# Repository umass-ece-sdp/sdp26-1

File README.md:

# SDP26 Team 1 | FALCON – Filming Autonomous Learning and Cinematic Optic Navigator

Autonomous DJI Tello target-tracking platform with a wearable glove controller. A Jetson host (or Linux laptop) runs vision and flight control while an ESP32-S3 glove sends discrete range commands over Wi-Fi. The system locks onto a target, keeps the subject centered and at a commanded distance, searches when lost, and lands safely on failure.

---

## Repository Map

- [software/src/main.py](software/src/main.py): Entry point - connects to Tello drone and ESP32 glove AP, starts the glove client and drone tracking threads
- [software/lib/falcon_vision.py](software/lib/falcon_vision.py): Vision + control loop, distance mapping from glove instructions, safety land/search logic
- [software/lib/falcon.py](software/lib/falcon.py): DJI Tello wrapper that auto-connects to the drone Wi-Fi using a provided interface/SSID
- [hardware/firmware](hardware/firmware): ESP32-S3 glove firmware with WiFi AP and TCP server, plus Python client for base station
- [software/scripts](software/scripts): Network helper scripts (WiFi AP setup for Tello and glove connections) and startup helper for the host
- [docs](docs): Design docs placeholders (currently empty); fill as deliverables are produced

---

## System Overview

- **Vision/Control (host):** Tracks a target in the Tello video feed, computes yaw/altitude/forward corrections, and commands the drone. Falls back to search spins when target is lost; lands after timeout or manual quit (press `q`). See [software/lib/falcon_vision.py](software/lib/falcon_vision.py).
- **Glove (ESP32-S3 DevKitC-1):** Four three-state switches encode a 4-char string (LR, FB, heading, altitude). Reads IMU and stretch sensors, computes hand velocity, packages data into 6-float packets, and sends to base station. Also creates the WiFi AP. See [hardware/firmware/main/glove.cpp](hardware/firmware/main/glove.cpp) and [hardware/firmware/main/wifi_server.cpp](hardware/firmware/main/wifi_server.cpp).
- **Networking:** The **ESP32 glove creates a WiFi AP** named **"FALCON-Glove"** (password: `team1-falcon`) on 192.168.4.0/24 and runs a **TCP server at 192.168.4.1:5000**. The **base station (host) connects as a client** to this AP and connects to the glove's TCP server. Separately, the base station connects to the Tello drone on its own WiFi SSID using a second interface. See [hardware/firmware/main/wifi_server.h](hardware/firmware/main/wifi_server.h) and [hardware/firmware/glove_client.py](hardware/firmware/glove_client.py) for configuration.

---

## Hardware

- DJI Tello drone.
- ESP32-S3-DevKitC-1 (Arduino/PlatformIO) running glove sensors and WiFi AP + TCP server.
- Four 3-state switches wired to pins (LR: GPIO4/5, FB: 6/7, Heading: 15/16, Altitude: 17/18). See [hardware/firmware/main/glove.cpp](hardware/firmware/main/glove.cpp).
- Host computer (Jetson Nano, Linux laptop, or Windows machine) with **two WiFi interfaces**: one for Tello drone, one for glove AP.

---

## Firmware (Glove) Setup

1. Install PlatformIO.
2. From [hardware/firmware](hardware/firmware):
   - Build: `platformio run -e client`
   - Flash: `platformio run -e client -t upload`
   - Serial monitor: `platformio device monitor -e client`
3. WiFi/Server config lives in [hardware/firmware/main/wifi_server.h](hardware/firmware/main/wifi_server.h):
   - **AP_SSID:** `FALCON-Glove` (the AP name the glove creates)
   - **AP_PASS:** `team1-falcon` (glove AP password)
   - **AP IP:** `192.168.4.1/24` (glove runs TCP server here)
   - **PORT:** `5000` (TCP server port on glove)
4. Glove reads sensors, creates a 6-float packet (fingers[4], speed, distance) every ~90ms, and sends it to any connected base station client. See [hardware/firmware/main/wifi_server.cpp](hardware/firmware/main/wifi_server.cpp).

---

## Software Prereqs

- Python 3.10+
- Dependencies: djitellopy, opencv-python, numpy, ultralytics (declared in [pyproject.toml](pyproject.toml)).

Install (recommended in a virtualenv):

```bash
pip install -e .
```

---

## Network Setup (Host / Base Station)

**Architecture:** Glove (ESP32) is the TCP server; base station (host) is the client.

### Prerequisites

- **Glove powered on first** — It creates AP "FALCON-Glove" and starts TCP server at 192.168.4.1:5000
- **Base station has two WiFi interfaces:**
  - **Interface 1:** Connects to Tello drone SSID (e.g., "TELLO-FE046A")
  - **Interface 2:** Connects to glove AP "FALCON-Glove"

### Automatic Setup (Linux with 2 interfaces)

```bash
sudo bash software/scripts/setup_wifi.sh TELLO-FE046A "" FALCON-Glove team1-falcon
```

This script:
1. Connects Interface 1 to Tello SSID
2. Connects Interface 2 to glove AP "FALCON-Glove"
3. Verifies connectivity to both networks

### Manual Setup (Windows or Single Interface)

**For Tello:**
1. Go to **Settings → Network & Internet → WiFi**
2. Connect to **TELLO-FE046A** (empty password)

**For Glove:**
1. Go to **Settings → Network & Internet → WiFi**
2. Connect to **FALCON-Glove** (password: `team1-falcon`)
3. You should get assigned an IP like 192.168.4.x

**Verify both connections:**
```bash
ping 192.168.1x.x.x.x     # Tello IP
ping 192.168.4.1          # Glove server
```

---

## Running the System

### Startup Sequence

1. **Power on the ESP32 glove first:**
   - Creates WiFi AP "FALCON-Glove"
   - Starts TCP server at 192.168.4.1:5000
   - Waits for base station client connection

2. **On the base station, ensure both WiFi connections are active:**
   - Connected to Tello SSID
   - Connected to "FALCON-Glove" AP

3. **Run the main program:**

   ```bash
   python -m software.src.main
   ```

   This will:
   - Connect to the Tello drone and request SDK mode
   - Connect to the glove's TCP server at 192.168.4.1:5000
   - Wait for glove connection (serial monitor should show "[SERVER] Base station connected from...")
   - Take off and begin tracking the target
   - Respond to glove sensor input and gesture commands

### Expected Output

**Glove Serial Monitor:**
```
[AP] Access Point created successfully!
[AP] SSID: FALCON-Glove
[AP] IP Address: 192.168.4.1
[SERVER] Base station connected from: 192.168.4.x
[SERVER] Sent packet (24 bytes)
```

**Base Station Terminal:**
```
[CLIENT] Connecting to glove server at 192.168.4.1:5000...
[CLIENT] Connected to glove server!
Binding complete
Connected with 192.168.4.1: 5000
```

---

## Glove Instruction Mapping (distance presets)

- `0000` → target distance 50 cm
- `1000` → target distance 25 cm
- `2000` → target distance 100 cm

Other patterns are logged but ignored for distance changes. The vision loop re-computes target area each time a mapped pattern arrives.

---

## Behavior and Safety

- Hover/search: If the target disappears, the drone yaws to search; after a timeout it lands.
- Manual exit: Press `q` in the vision window to land and stop.
- Connection failures: Tello Wi-Fi connect failures abort startup; glove disconnects clear the shared state in [software/lib/variables.py](software/lib/variables.py).
- Stream cleanup: On any exit path, video stream is stopped and RC commands zeroed before ending.

---

## Development Notes

- Vision currently uses HSV color masking; YOLO detection code is present but commented out. Tweak target color, tolerances, and speeds near the top of [software/lib/falcon_vision.py](software/lib/falcon_vision.py).
- Empty doc folders contain `.gitkeep`; populate [docs/design_specs](docs/design_specs) and [docs/final_report](docs/final_report) as artifacts are produced.
- No automated tests yet; add unit tests under `software/tests/` and leverage PlatformIO monitors for firmware.

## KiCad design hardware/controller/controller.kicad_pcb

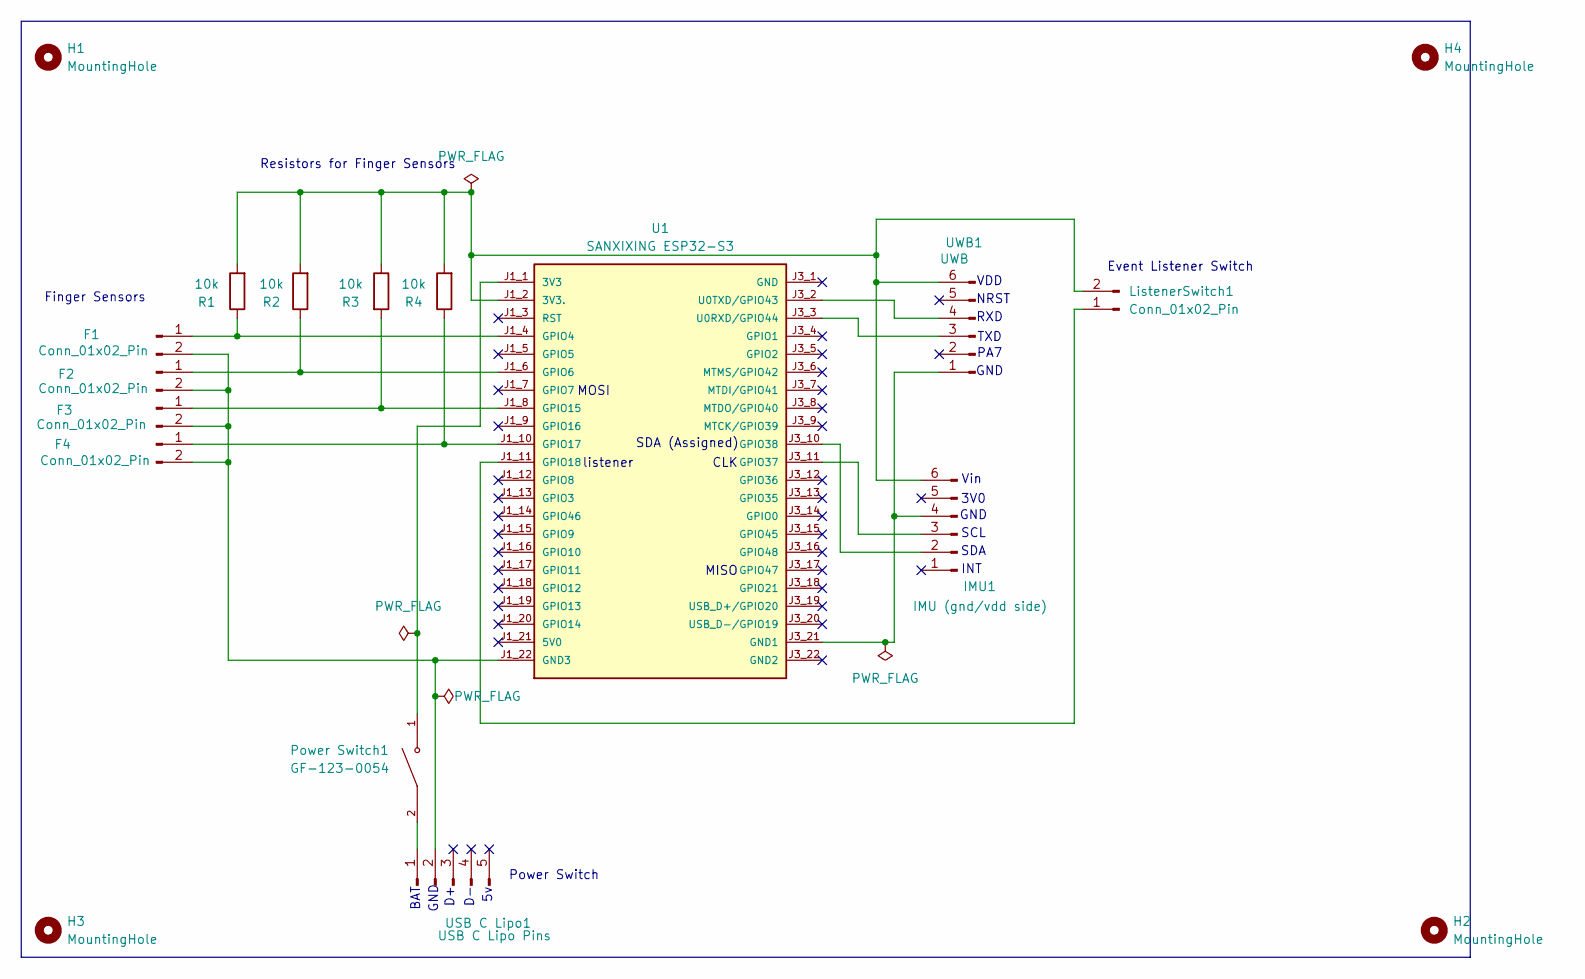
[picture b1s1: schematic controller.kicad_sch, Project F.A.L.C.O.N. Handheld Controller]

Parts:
F1, F2, F3, F4: Conn_01x02_Pin; PinSocket_1x02_P2.54mm_Vertical
H1, H2, H3, H4: MountingHole; MountingHole_3.2mm_M3
IMU1: IMU (gnd/vdd side); PinSocket_1x06_P2.54mm_Vertical
ListenerSwitch1: Conn_01x02_Pin; PinSocket_1x02_P2.54mm_Vertical
Power Switch1: GF-123-0054; SW_GF-123-0054; PARTREV May 20, 2003
R1, R2, R3, R4: 10k; R_Axial_DIN0204_L3.6mm_D1.6mm_P5.08mm_Horizontal
U1: SANXIXING ESP32-S3; SANXIXING-ESP32-S3
USB C Lipo1: USB C Lipo Pins; PinSocket_1x05_P2.54mm_Vertical
UWB1: UWB; PinSocket_1x06_P2.54mm_Vertical

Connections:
unnamed 0: F1.1, R1.1, U1.J1_4 (GPIO4); also elsewhere on the board
unnamed 1: F1.2, F2.2, F3.2, F4.2, U1.J1_22 (GND3), USB C Lipo1.2; also elsewhere on the board
unnamed 2: F2.1, R2.1, U1.J1_6 (GPIO6); also elsewhere on the board
unnamed 3: F3.1, R3.2, U1.J1_8 (GPIO15); also elsewhere on the board
unnamed 4: F4.1, R4.1, U1.J1_10 (GPIO17); also elsewhere on the board
unnamed 5: IMU1.2, U1.J3_10 (GPIO38); also elsewhere on the board
unnamed 6: IMU1.3, U1.J3_11 (GPIO37); also elsewhere on the board
unnamed 7: IMU1.4, U1.J3_21 (GND1), UWB1.1; also elsewhere on the board
unnamed 8: IMU1.6, ListenerSwitch1.2, R1.2, R2.2, R3.1, R4.2, U1.J1_2 (3V3.), UWB1.6; also elsewhere on the board
unnamed 9: ListenerSwitch1.1, U1.J1_11 (GPIO18); also elsewhere on the board
unnamed 10: Power Switch1.1, U1.J1_1 (3V3); also elsewhere on the board
unnamed 11: U1.J3_3 (U0RXD/GPIO44), UWB1.3; also elsewhere on the board
unnamed 12: U1.J3_2 (U0TXD/GPIO43), UWB1.4; also elsewhere on the board
unnamed: Power Switch1.2, USB C Lipo1.1

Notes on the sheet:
INT
TXD
Power Switch
VDD
NRST
GND
Vin
PA7
SDA
MISO
SCL
3V0
BAT
Resistors for Finger Sensors
Event Listener Switch
SDA (Assigned)
MOSI
RXD
CLK
listener
Finger Sensors

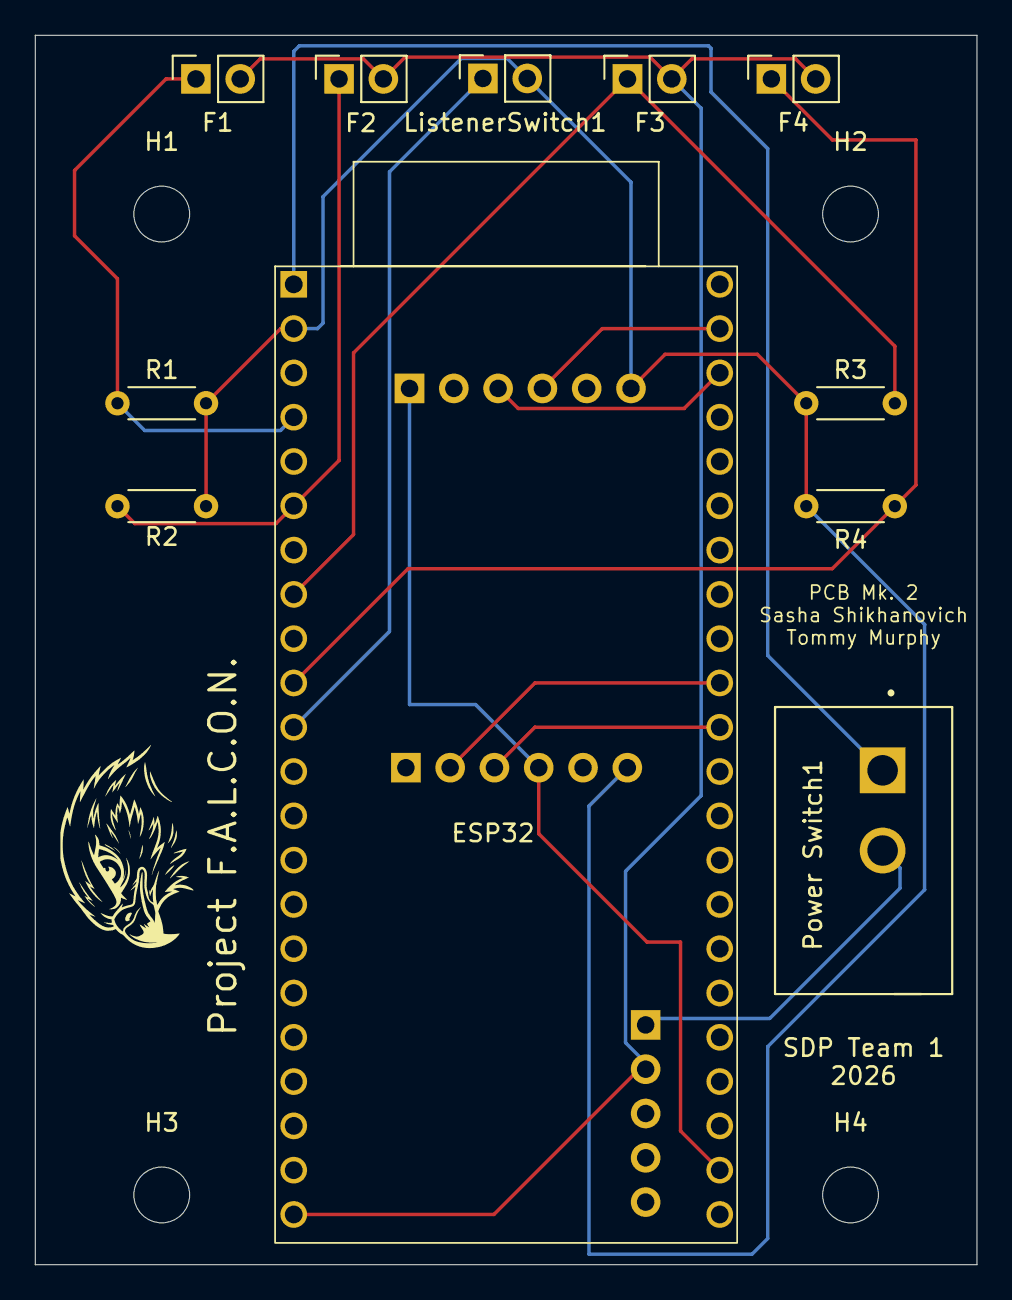
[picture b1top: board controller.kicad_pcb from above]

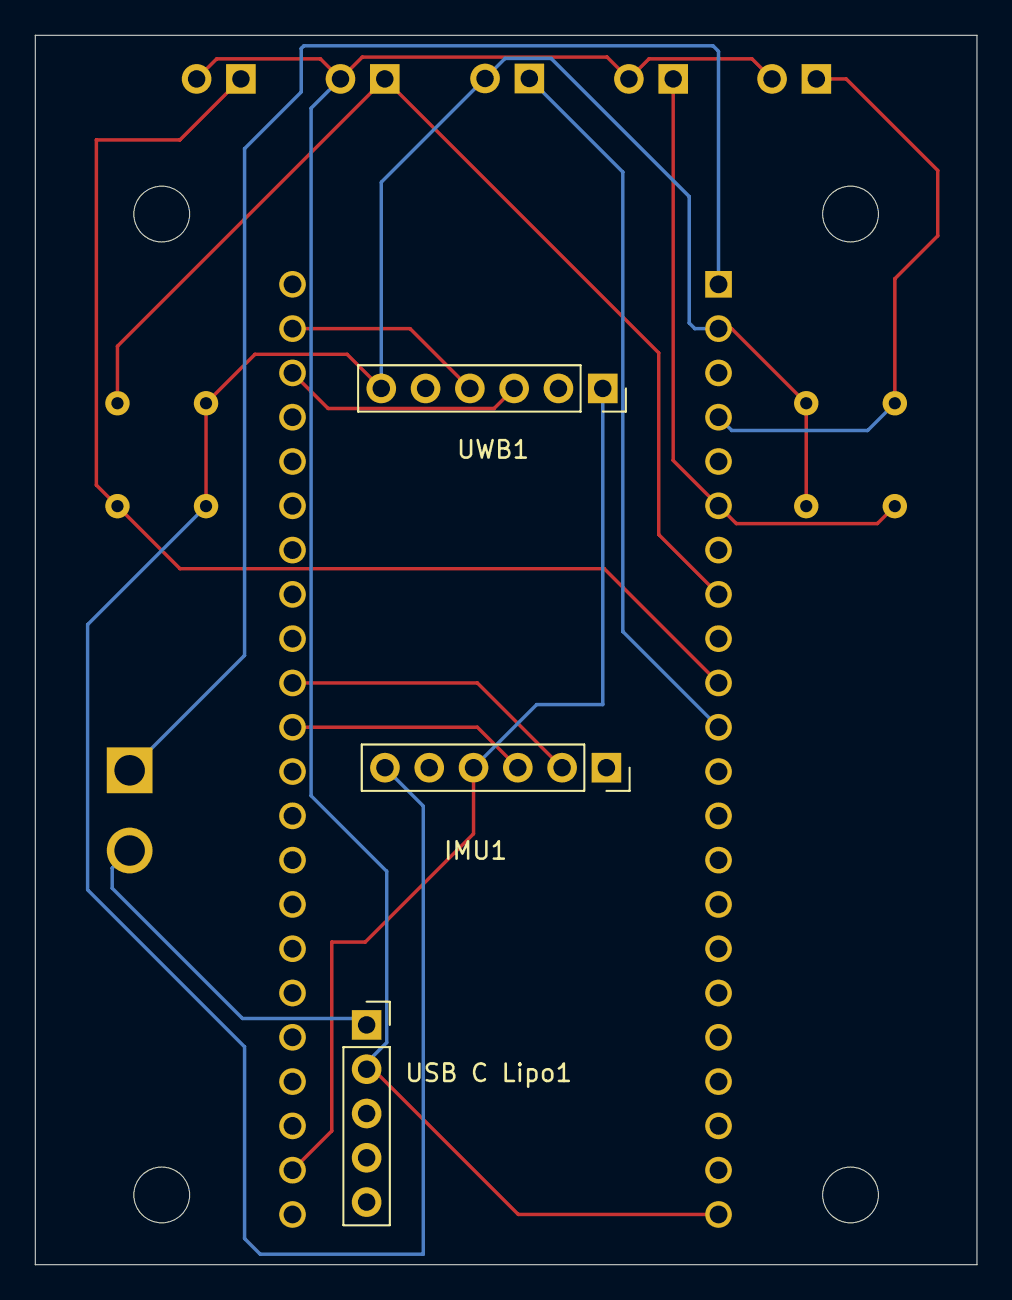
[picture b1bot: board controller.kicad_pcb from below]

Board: 2 copper layers, 54.0 x 70.5 mm, 19 parts (3 on the bottom side), 14 nets.

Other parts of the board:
ESP32: SANXIXING ESP32-S3; SANXIXING-ESP32-S3
Project F.A.L.C.O.N.: LOGO

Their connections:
unnamed 0: ESP32.J1_4 (GPIO4); also elsewhere on the board
unnamed 1: ESP32.J1_22 (GND3); also elsewhere on the board
unnamed 2: ESP32.J1_6 (GPIO6); also elsewhere on the board
unnamed 3: ESP32.J1_8 (GPIO15); also elsewhere on the board
unnamed 4: ESP32.J1_10 (GPIO17); also elsewhere on the board
unnamed 5: ESP32.J3_10 (GPIO38); also elsewhere on the board
unnamed 6: ESP32.J3_11 (GPIO37); also elsewhere on the board
unnamed 7: ESP32.J3_21 (GND1); also elsewhere on the board
unnamed 8: ESP32.J1_2 (3V3.); also elsewhere on the board
unnamed 9: ESP32.J1_11 (GPIO18); also elsewhere on the board
unnamed 10: ESP32.J1_1 (3V3); also elsewhere on the board
unnamed 11: ESP32.J3_3 (U0RXD/GPIO44); also elsewhere on the board
unnamed 12: ESP32.J3_2 (U0TXD/GPIO43); also elsewhere on the board

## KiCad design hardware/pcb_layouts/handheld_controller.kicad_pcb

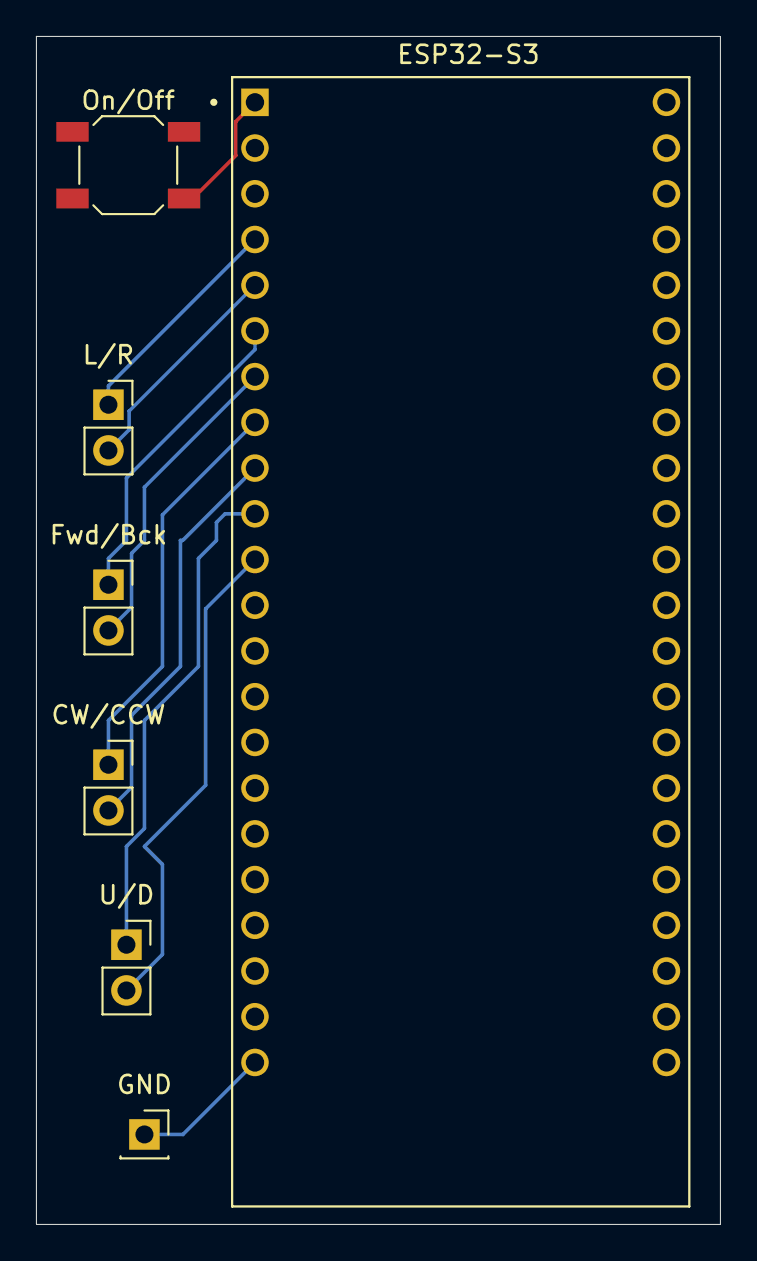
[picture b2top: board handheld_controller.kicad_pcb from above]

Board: 2 copper layers, 38.0 x 66.0 mm, 7 parts (0 on the bottom side), 10 nets.

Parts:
CW/CCW: Conn_01x02_Pin; PinSocket_1x02_P2.54mm_Vertical
ESP32-S3: ESP32-S3-DEVKITC-1-N8R8
Fwd/Bck: Conn_01x02_Pin; PinSocket_1x02_P2.54mm_Vertical
GND: Conn_01x01_Pin; PinSocket_1x01_P2.54mm_Vertical
L/R : Conn_01x02_Pin; PinSocket_1x02_P2.54mm_Vertical
On/Off: SW_DIP_x01; SW_SPST_SKQG_WithStem
U/D: Conn_01x02_Pin; PinSocket_1x02_P2.54mm_Vertical

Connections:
GND: ESP32-S3.J1_22 (GND3), GND.1
unnamed: ESP32-S3.J1_4 (GPIO4), L/R.1
unnamed: ESP32-S3.J1_5 (GPIO5), L/R.2
unnamed: ESP32-S3.J1_6 (GPIO6), Fwd/Bck.1
unnamed: ESP32-S3.J1_7 (GPIO7), Fwd/Bck.2
unnamed: CW/CCW.1, ESP32-S3.J1_8 (GPIO15)
unnamed: CW/CCW.2, ESP32-S3.J1_9 (GPIO16)
unnamed: ESP32-S3.J1_10 (GPIO17), U/D.1
unnamed: ESP32-S3.J1_11 (GPIO18), U/D.2
unnamed: ESP32-S3.J1_1 (3V3), On/Off.2

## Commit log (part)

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2025-10-06 Starting code for ACD functions
2025-10-21 initial hardware commit, basic hardware block schem
2025-10-21 Create task of connecting wifi in python
2025-10-21 Change project name
2025-10-21 Inital code for Docker Container
2025-10-22 Added started code for ESP32 WiFi client
2025-10-22 Added bash script for adding connecting to drone's wifi
2025-10-22 Added file searching to get .sh
2025-10-23 Set Falcon to always connect with on-board port
2025-10-23 3d model file
2025-10-23 Some changes to run docker in linux
2025-10-23 Change WiFi to recognize path from root
2025-10-24 Add exit on connection error
2025-10-24 init commit of cv shi
2025-10-24 simplified and documented code
2025-10-24 moved a couple params
2025-11-02 Created pio project for compiling and flashing client code
2025-11-02 Remove old client code (i forgor)
2025-11-02 Switch client to sending strings
2025-11-02 Create/run server to receive instructions from glove
2025-11-03 Move FALCON to lib directory
2025-11-03 Create variables file for shared environment
2025-11-03 Integrate variables into server code
2025-11-03 Start a main file for linking systems
2025-11-04 adding hardware controller serial code
2025-11-04 Link together systems, split into processes
2025-11-04 downloaded yolo locally and searched for it locally
2025-11-04 changed file pathing
2025-11-04 Move/rename glove code
2025-11-04 maybe fixed color tracking issue
2025-11-04 final (ish) schematic with real footprints
2025-11-04 initial pcb file commit
2025-11-04 Changed frame presentation to viewer
2025-11-04 Moved vision code to lib
2025-11-06 acceptably final PCB (passes DRC)
2025-11-06 acceptably final schematic (passes ERC)
2025-11-07 debugging print statements
2025-11-07 update gitignore
2025-11-07 adding main and changing .ini to mac paths
2025-11-07 Created header files for firmware
2025-11-07 Changes to run main in ini
2025-11-07 convert espidf code to arduino
2025-11-07 trying to convert glove code to esp framework (idk if it works)
2025-11-07 using one gitignore
2025-11-07 working connection using arduino
2025-11-11 Add dynamic COM port finding for windows, removed espidf files
2025-11-11 Changing default wifi interface
2025-11-11 print instructions from esp
2025-11-11 adding toml to package falcon
2025-11-11 Added loop for drone process
2025-11-11 Adding sleep
2025-11-11 Revert "Merge branch 'integration-testing' into converting-to-arduino"
    This reverts commit dbe07ec8ee8ab3334bb31f3c9234bafc4f2a2372, reversing
    changes made to 41b58e3be06abe35e6818b64846f8ce6c7973896.
2025-11-11 adding led library
2025-11-12 updating color codes for signal transmission debugging
2025-11-12 stable color set to blue
2025-11-14 Update wifi connection function
2025-11-14 possible change to fix color code debugging
2025-11-14 forgot wifi_client in last commit
2025-11-14 Startup Script
2025-11-14 Build wheel
2025-11-14 adding debug statements
2025-11-14 changing file permissions
2025-11-14 Update falcon_vision
2025-11-14 Change wifi name
2025-11-14 Update Python version
2025-11-14 Update filepathing
2025-11-14 Fixed pathing fr
2025-11-14 Add ssid as parameter to class
2025-11-14 Add scripts to toml
2025-11-14 Add scripts fr now
2025-11-14 Update pathing
2025-11-14 Turn off socket
2025-11-14 Adding wifi connection to vision
2025-11-14 Fixed path
2025-11-14 Remove self
2025-11-14 pathing
2025-11-14 Fix filepathing for YOLO
2025-11-14 preliminary glove instruction implementation
2025-11-19 Potential connection fix
2025-11-19 New wheel
2025-11-20 Remove shared dict dependency
2025-11-20 Fixed line endings
2025-11-20 Fix line endings in shell scripts and add .gitattributes
2025-11-20 Attempt at fixing interface issues
2025-11-20 Use tello's socket control, use bash to ensure Linux routes packets correctly
2025-11-20 Fixing connection order
2025-11-20 Debugging statements
2025-11-20 Finally getting somewhere
2025-11-20 Remove old action dict
2025-11-20 Add shared_dict back to vision
2025-11-20 Update project version
2025-11-20 Fixed ip address
2025-11-20 Fixed server ip
2025-11-20 Fix hostname
2025-12-01 Changed dist_map to match glove output
2025-12-01 Added wait condition for glove connection
2025-12-02 Switch from processes to threads, allows use of global variables
2025-12-02 Build updated wheel
2025-12-02 Add standalone server testing
2025-12-02 Fix running of server
2025-12-02 Added configuring AP's IP addr to main
2025-12-02 Fix filepathing
2025-12-02 Use sudo in script
2025-12-02 Stop tracking .vscode
2025-12-02 Changed glove code to send real data
2025-12-02 Added an environment to compile and upload main.cpp
2025-12-02 Remove loop in client (send once per request)
2025-12-02 implemented proportional derivated feedback control
2025-12-02 removed some things that aren't used and slowed down the script potentially
2025-12-02 second version of falcon vision that could be better
2025-12-02 Reverting error in glove code
2025-12-02 Changed distance mapping
2025-12-02 Wait for drone to be on and connected before spamming instructions
2025-12-02 Set drone state to off
2025-12-03 Change version numbering
2025-12-03 Explicitly set instructions to string
2025-12-03 Debugging
2025-12-03 Fix window size
2025-12-03 Changed print statement to be more descriptive
2025-12-03 Using falcon_vision2
2025-12-03 Fixing issue with instructions not being read
2025-12-04 make three versions of falcon_vision
2025-12-04 Wheel for prev commit
2025-12-04 Specify color at runtime
2025-12-04 Changed color input method
2025-12-04 Error
2025-12-04 Reverting attempts at color assignment
2025-12-04 Using green as target color
2025-12-04 trying yellow
2025-12-04 trying red
2025-12-04 Changing color to pink, changed distance mappings
2025-12-05 Set color to red
2025-12-05 Changing starting distances
2026-01-19 Version 0.1.0
2026-02-17 Early controller design
2026-02-19 Create scripts for networking setup/exit
2026-02-19 Add/change functions in falcon to use new scripts
2026-02-19 Fix IP address for ESP32
2026-02-19 Alter falcon_vision and main to use new scripts
2026-02-19 Remove old scripts, update version
2026-02-22 RYUW122 UWB Module Documentation
2026-02-22 PCB Redesign for UWB Module
2026-02-23 Test code for finger/imu sensors
2026-02-23 Updated code for glove firmware, needs testing
2026-02-23 Update server-side receival of instructions
2026-02-23 Initial Kalman Filter
2026-02-23 Added AI comments to EKF to help with understanding, added function to get output
2026-02-24 removing legacy folders
2026-02-25 adding all part ready for schem layout
2026-02-25 adding labels and swapping power switch on schem
2026-02-26 starting routing on schem
2026-02-26 Create a fiducial class for target tracking
2026-02-26 Update EKF with proper units (cm)
2026-02-26 Add target tracking/finger mapping to FALCON
2026-02-26 Update main to use FALCON for target tracking
2026-02-26 Use GIL in shared dictionary
2026-02-26 Test script for PCB
2026-02-26 Changed accel library
2026-02-26 Fixed glove to use MPU-6050
2026-02-26 Updated main to use MPU-6050
2026-02-26 Update server and variables to include gyro measurements
2026-02-26 Move EKF and FIducial declarations to __init__
2026-02-26 schem wiring should be done
2026-02-26 AI gyro addition to EKF
2026-02-26 some ERC resolved, checkpoint
2026-03-02 init commit
2026-03-02 generate 4 fiducials
2026-03-02 Update README.md with project overview, repository structure, and setup instructions; remove unnecessary files from hardware/controller
2026-03-02 ESP32-S3 datasheet
2026-03-02 Cleanup readme
2026-03-02 README updates
2026-03-02 updated fiducial class with accurate distance estimation and fiducial generation
2026-03-02 forgot to remove line from falcon.py
2026-03-02 fixed bad indentation in fiducials.py, renamed function call in falcon.py
2026-03-02 added a fiducial detection test file
2026-03-02 removed more boilerplate
2026-03-02 Update README to clarify design docs status
    Removed 'currently empty' from design docs placeholders.
2026-03-02 Update development notes in README.md
    Clarify development notes regarding documentation and testing.
2026-03-03 Update fiducial filepaths
2026-03-09 Fixed rotation matrix frame, made preflight sim give more meaningful outputs
2026-03-10 Remove unnecessary variables.py
2026-03-10 Switch from threading -> multiprocessing
2026-03-11 schematic ERC passed
2026-03-11 PCB placement done
2026-03-11 PCB routing checkpoint 1
2026-03-11 routing checkpoint 2
2026-03-11 routing done
2026-03-12 routing and screw hole placement done
2026-03-14 edits made, PCB ready for 1st run
2026-03-20 added fab files
2026-03-24 Broke some code down into functions
2026-03-25 pushing script files for cdr. faster_tracking is best one
2026-03-29 Added faster_tracking to falcon.py
2026-03-29 Created WifiManager classes to assign interfaces
2026-03-29 Added video saving ability, uses threading
2026-03-29 curve track script
2026-03-29 cdr vid cuh
2026-04-02 Python script for programming UWB modules
2026-04-02 Add function for getting distance readings from UWB
2026-04-02 Update test script to find UWB distance
2026-04-02 Added glove to test env
2026-04-02 Refactor pin definitions in test.cpp and update platformio.ini for improved clarity; add .gitignore and extensions.json for project configuration
2026-04-02 nicks tuff and did all the work
2026-04-08 save video work (threads) yay
2026-04-09 Switching IMU library
2026-04-09 all sensors working, stable accel readouts to serial
2026-04-09 event listener switch functional
2026-04-09 schem fixed, ready to route
2026-04-09 redesign of part placements on PCB, measurement confirmed
2026-04-09 Removed gyro readings from packet being sent/received
2026-04-09 Incorporated accel filtering into glove.cpp, redesigned test script
2026-04-09 Adjusted server code to receive speed instead of IMU data
2026-04-09 PCB routing done
2026-04-09 Added debug mode to server.py
2026-04-09 Main script successfully sends data from glove to server
2026-04-09 Added scripts for setting up/taking down wifi interface in AP mode
2026-04-09 kinda a shitshow, need to reroute after adding terminal blocks
2026-04-09 Changing power pins for battery
2026-04-09 pcb placed, routed, designs and text added (DIMENSION CHECK NEEDED)
2026-04-10 routing and placing checkpoint, should be ready for fab
2026-04-14 Tuned filter
2026-04-15 better arcing
2026-04-16 Time between packets down to ~500ms
2026-04-20 Remove UWB distance readings from main
2026-04-20 cleaned script untested
2026-04-20 ai did this
2026-04-20 ai did this too but i like it more
2026-04-21 Implemented gesture reading
2026-04-21 UNTESTED - Scripts for simple wifi setup and reset
2026-04-22 Network speed updates
2026-04-22 Testing changes
2026-04-22 better arcing and final cleaned scropt work
2026-04-22 Changed glove HOST_IP
2026-04-22 setupwifi works with falcon
2026-04-22 server fixes
2026-04-23 Minor improvements/resets
2026-04-23 Make drone main thread
2026-04-23 Remove old files
2026-04-23 Wifi scripts to connect to drone and glove
2026-04-23 Remove old scripts
2026-04-23 Remove auto wifi connection
2026-04-24 Test script updates
2026-04-27 logic for smaller fiducial on shoulders, still need to update final size of each type of fiducal
2026-04-28 Fix thresholds, print commands
2026-04-28 Removed toggle, hold for listening
2026-04-28 Fixed codec order
2026-04-28 changed allowed fiducials for arcing
2026-04-28 Only reads hand instructions when button is pressed
2026-04-29 itowrksfuckme
2026-04-29 All-in-one demo day script
2026-04-29 Script for connecting to/reading from the glove
2026-04-29 drone demo script
2026-04-29 glove demo script
2026-04-29 thresholds-for-sash
2026-04-29 further and closer commands
2026-04-29 added up and down commands
2026-04-29 PID speed bc fuck it
2026-04-30 glove calibration function
2026-04-30 added glove calibration to demo script and incorporated commands to window
2026-04-30 deleted import
2026-04-30 glove demo improvements
